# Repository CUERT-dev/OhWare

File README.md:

View this project on [CADLAB.io](https://cadlab.io/project/29674). 

# ObcSimplex

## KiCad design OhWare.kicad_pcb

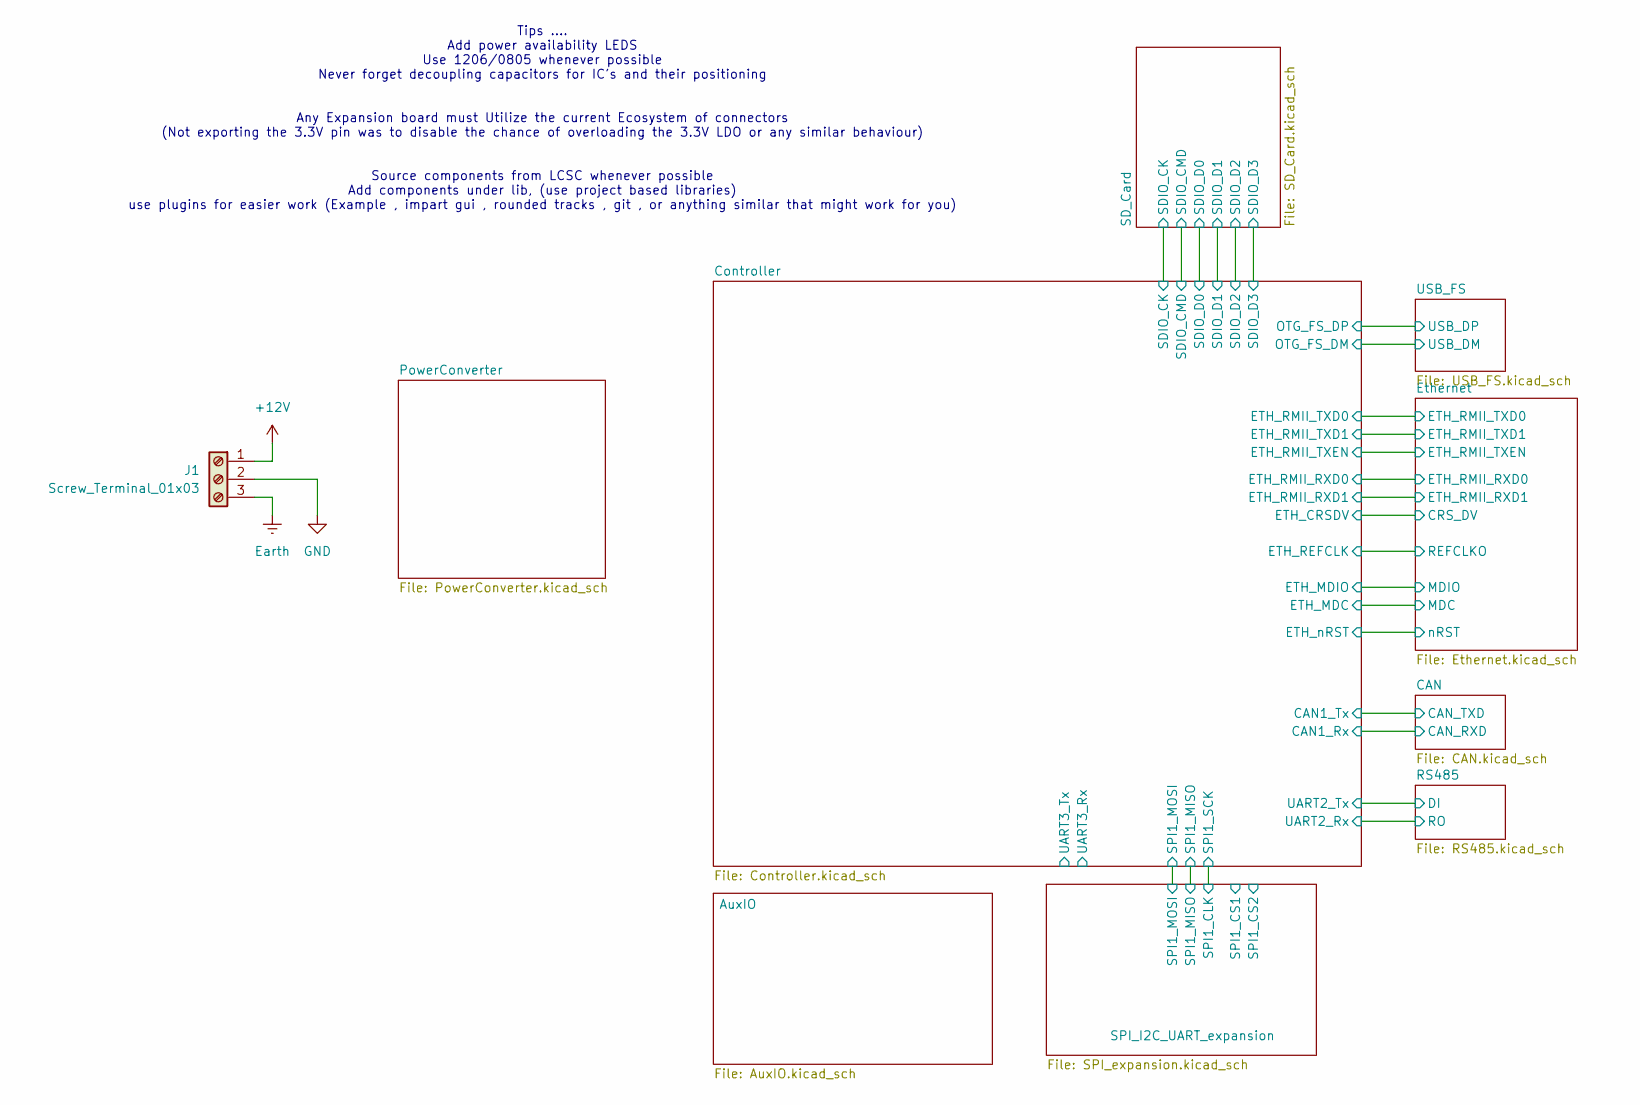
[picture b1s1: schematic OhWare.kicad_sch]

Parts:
J1: Screw_Terminal_01x03

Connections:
+12V: J1.1; also elsewhere on the board

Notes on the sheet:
Tips .... Add power availability LEDS Use 1206/0805 whenever possible Never forget decoupling capacitors for IC's and their positioning Any Expansion board must Utilize the current Ecosystem of connectors (Not exporting the 3.3V pin was to disable the chance of overloading the 3.3V LDO or any simil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

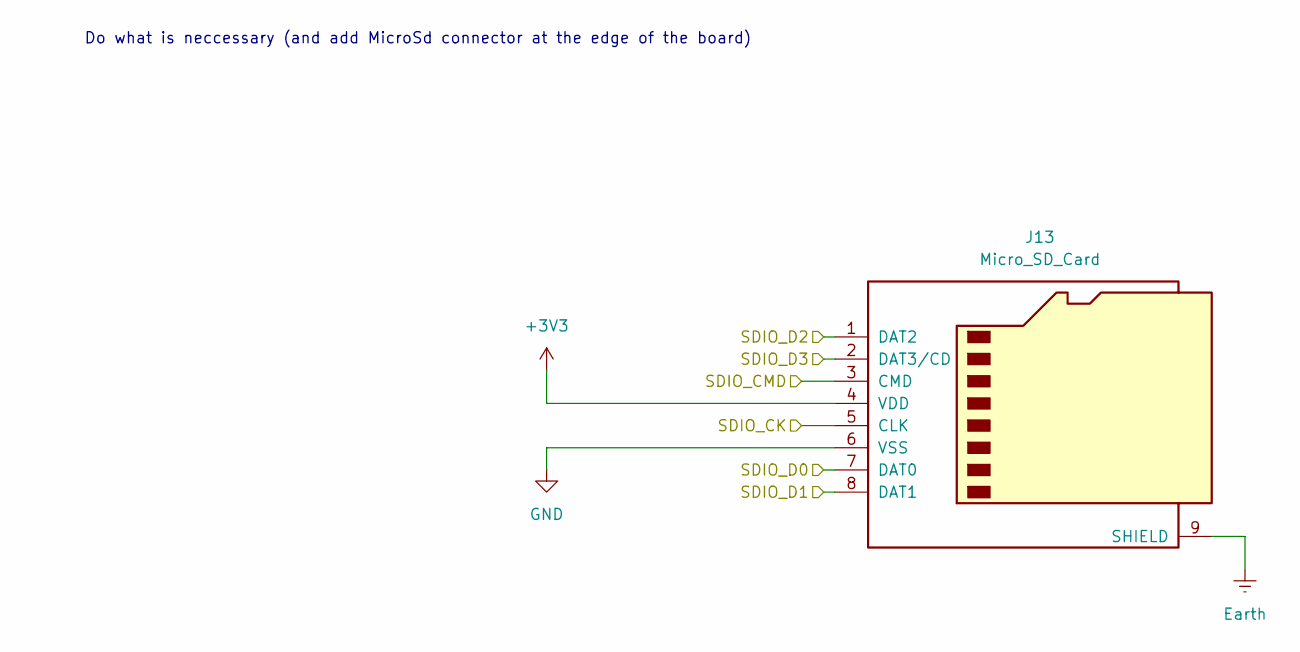
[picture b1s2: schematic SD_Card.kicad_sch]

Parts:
J13: Micro_SD_Card; microSD_HC_Molex_47219-2001

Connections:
+3V3: J13.4 (VDD); also elsewhere on the board
/Controller/SDIO_CK: J13.5 (CLK); also elsewhere on the board
/Controller/SDIO_CMD: J13.3 (CMD); also elsewhere on the board
/Controller/SDIO_D0: J13.7 (DAT0); also elsewhere on the board
/Controller/SDIO_D1: J13.8 (DAT1); also elsewhere on the board
/Controller/SDIO_D2: J13.1 (DAT2); also elsewhere on the board
/Controller/SDIO_D3: J13.2 (DAT3/CD); also elsewhere on the board

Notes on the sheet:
Do what is neccessary (and add MicroSd connector at the edge of the board)

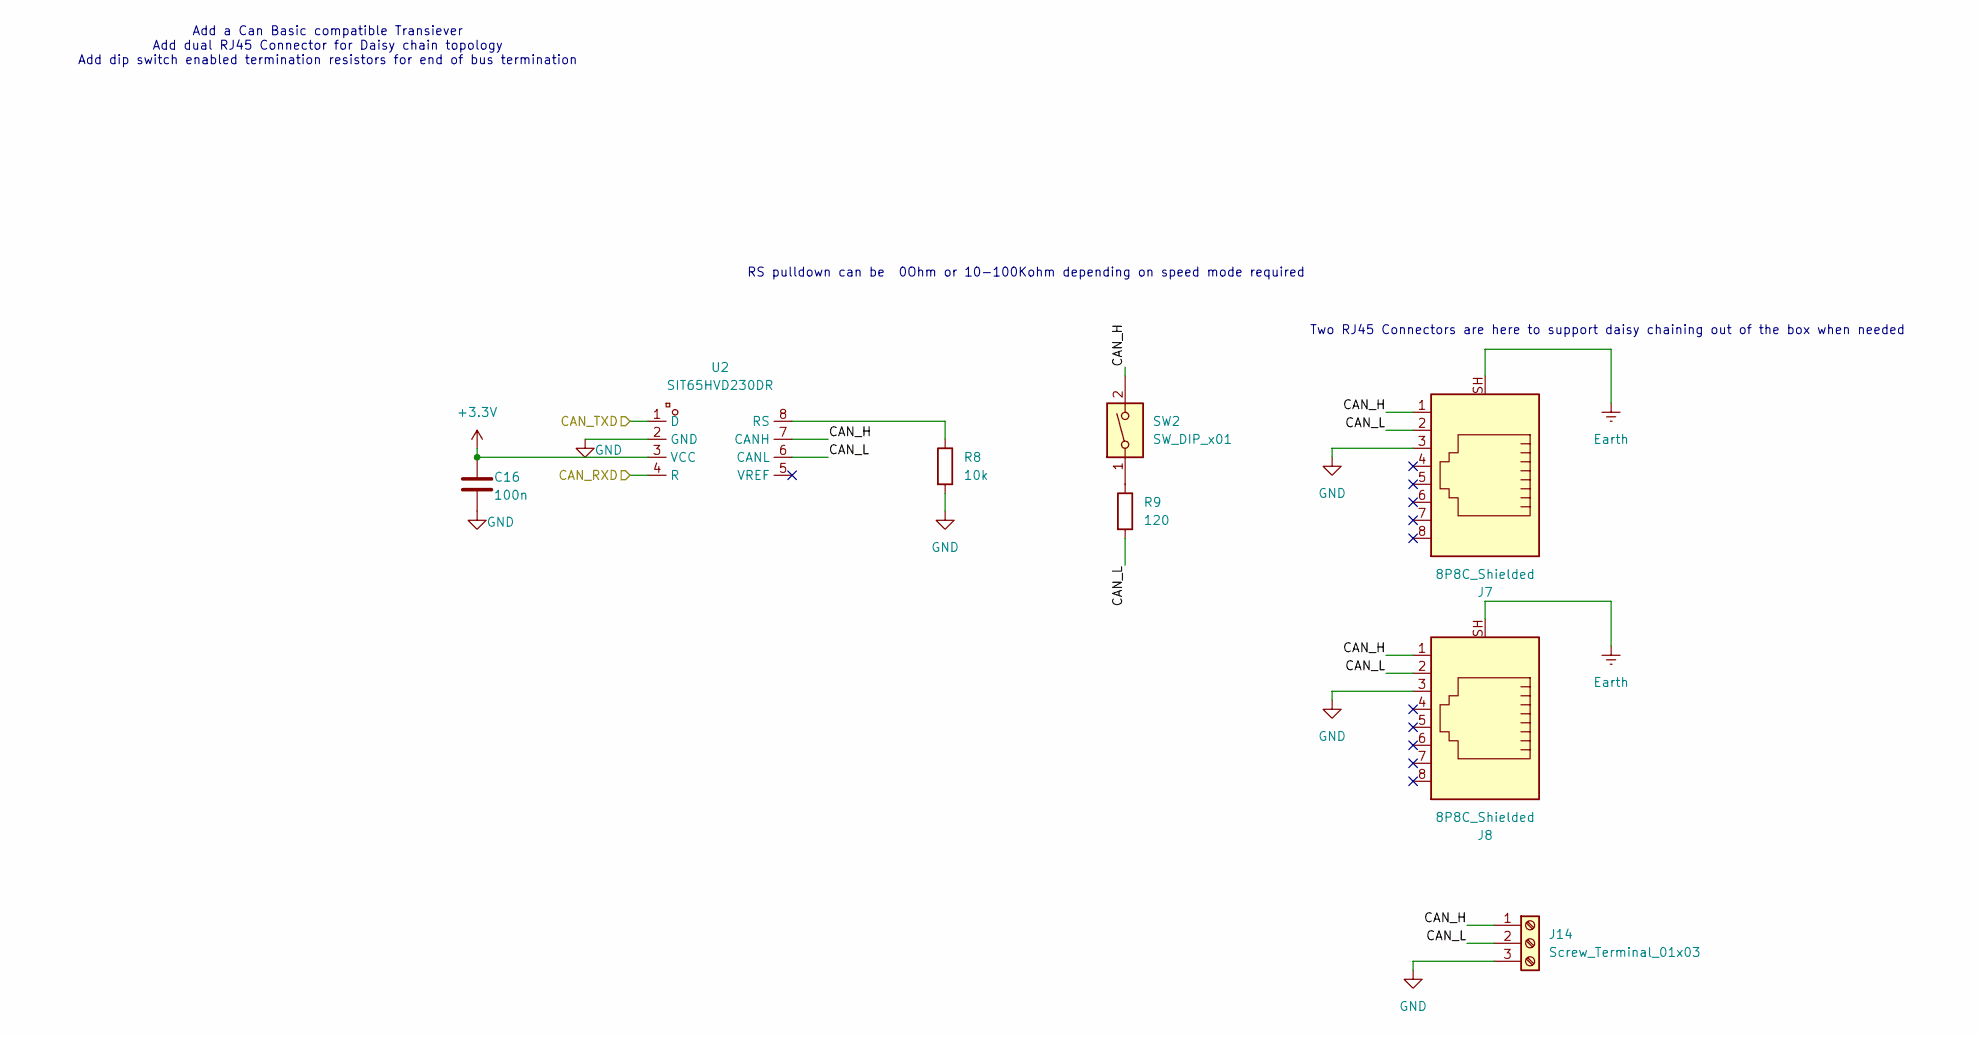
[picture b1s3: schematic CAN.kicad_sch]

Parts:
C16: 100n; C_0805_2012Metric
J7, J8: 8P8C_Shielded; RJ45_Ninigi_GE
J14: Screw_Terminal_01x03; TerminalBlock_Phoenix_PT-1,5-3-3.5-H_1x03_P3.50mm_Horizontal
R8: 10k; R_0805_2012Metric
R9: 120; R_0805_2012Metric
SW2: SW_DIP_x01; SW_DIP_SPSTx01_Slide_6.7x4.1mm_W7.62mm_P2.54mm_LowProfile
U2: SIT65HVD230DR; SOP-8_L4.9-W3.9-P1.27-LS6.0-BL; LCSC Part C496619

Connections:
+3.3V: C16.1, U2.3 (VCC); also elsewhere on the board
/CAN/CAN_L: J7.2, J8.2, J14.2, R9.2, U2.6 (CANL)
/CAN/CAN_RXD: U2.4 (R); also elsewhere on the board
/CAN/CAN_TXD: U2.1 (D); also elsewhere on the board
unnamed: R8.1, U2.8 (RS)

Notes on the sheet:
Add a Can Basic compatible Transiever Add dual RJ45 Connector for Daisy chain topology Add dip switch enabled termination resistors for end of bus termination
RS pulldown can be 0Ohm or 10-100Kohm depending on speed mode required
Two RJ45 Connectors are here to support daisy chaining out of the box when needed

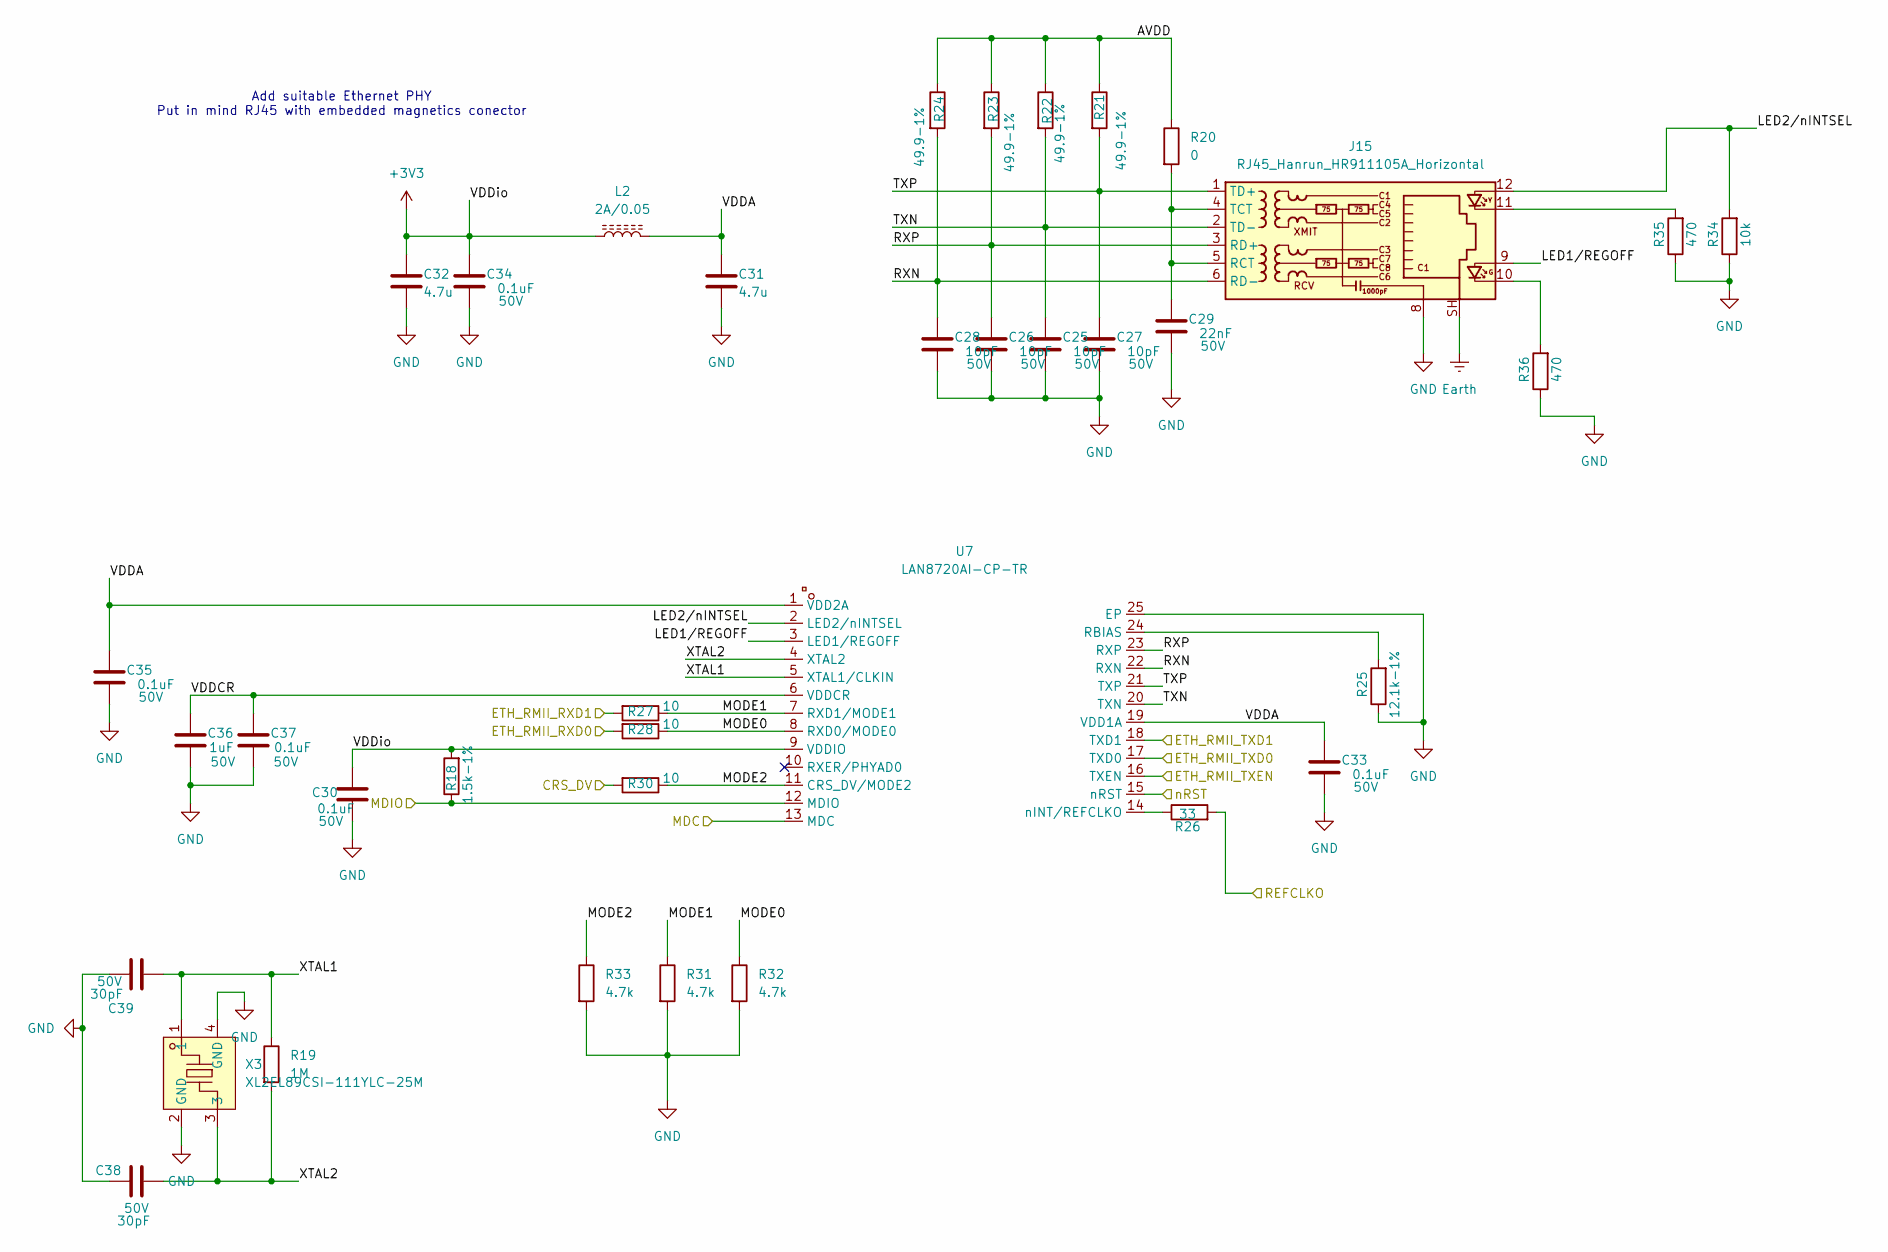
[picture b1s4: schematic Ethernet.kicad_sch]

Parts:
C25, C26, C27, C28: 10pF; C_0805_2012Metric; Voltage Rating 50V
C29: 22nF; C_0805_2012Metric; Voltage Rating 50V
C30, C33, C34, C35, C37: 0.1uF; C_0805_2012Metric; Voltage Rating 50V
C31, C32: 4.7u; C_0805_2012Metric
C36: 1uF; C_0805_2012Metric; Voltage Rating 50V
C38, C39: 30pF; C_0805_2012Metric; Voltage Rating 50V
J15: RJ45_Hanrun_HR911105A_Horizontal
L2: 2A/0.05; L_1206_3216Metric
R18: 1.5k-1%; R_0805_2012Metric
R19: 1M; R_0805_2012Metric
R20: 0; R_0805_2012Metric
R21, R22, R23, R24: 49.9-1%; R_0805_2012Metric
R25: 12.1k-1%; R_0805_2012Metric
R26: 33; R_0805_2012Metric
R27, R28, R30: 10; R_0805_2012Metric
R31, R32, R33: 4.7k; R_0805_2012Metric
R34: 10k; R_0805_2012Metric
R35, R36: 470; R_0805_2012Metric
U7: LAN8720AI-CP-TR; QFN-24_L4.0-W4.0-P0.50-BL-EP2.6; LCSC Part C17146
X3: XL2EL89CSI-111YLC-25M; CRYSTAL-SMD_4P-L3.2-W2.5-BL; LCSC Part C5280577

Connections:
+3V3: C30.1, C32.1, C34.1, L2.1, R18.2, U7.9 (VDDIO); also elsewhere on the board
/Controller/ETH_CRSDV: R30.2; also elsewhere on the board
/Controller/ETH_MDC: U7.13 (MDC); also elsewhere on the board
/Controller/ETH_MDIO: R18.1, U7.12 (MDIO); also elsewhere on the board
/Controller/ETH_REFCLK: R26.2; also elsewhere on the board
/Controller/ETH_RMII_RXD0: R28.2; also elsewhere on the board
/Controller/ETH_RMII_RXD1: R27.2; also elsewhere on the board
/Controller/ETH_RMII_TXD0: U7.17 (TXD0); also elsewhere on the board
/Controller/ETH_RMII_TXD1: U7.18 (TXD1); also elsewhere on the board
/Controller/ETH_RMII_TXEN: U7.16 (TXEN); also elsewhere on the board
/Controller/ETH_nRST: U7.15 (nRST); also elsewhere on the board
/Ethernet/AVDD: R20.1, R21.1, R22.1, R23.1, R24.1
/Ethernet/LED1/REGOFF: J15.9, U7.3 (LED1/REGOFF)
/Ethernet/LED2/nINTSEL: J15.12, R34.2, U7.2 (LED2/nINTSEL)
/Ethernet/MODE0: R28.1, R32.1, U7.8 (RXD0/MODE0)
/Ethernet/MODE1: R27.1, R31.1, U7.7 (RXD1/MODE1)
/Ethernet/MODE2: R30.1, R33.1, U7.11 (CRS_DV/MODE2)
/Ethernet/RXN: C28.1, J15.6 (RD-), R24.2, U7.22 (RXN)
/Ethernet/RXP: C26.1, J15.3 (RD+), R23.2, U7.23 (RXP)
/Ethernet/TXN: C25.1, J15.2 (TD-), R22.2, U7.20 (TXN)
/Ethernet/TXP: C27.1, J15.1 (TD+), R21.2, U7.21 (TXP)
/Ethernet/VDDA: C31.1, C33.1, C35.1, L2.2, U7.1 (VDD2A), U7.19 (VDD1A)
/Ethernet/VDDCR: C36.1, C37.1, U7.6 (VDDCR)
/Ethernet/XTAL1: C39.2, R19.1, U7.5 (XTAL1/CLKIN), X3.1
/Ethernet/XTAL2: C38.2, R19.2, U7.4 (XTAL2), X3.3
unnamed: J15.10, R36.2
unnamed: J15.11, R35.2
unnamed: C29.1, J15.4 (TCT), J15.5 (RCT), R20.2
unnamed: R25.2, U7.24 (RBIAS)
unnamed: R26.1, U7.14 (nINT/REFCLKO)

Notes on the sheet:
Add suitable Ethernet PHY Put in mind RJ45 with embedded magnetics conector

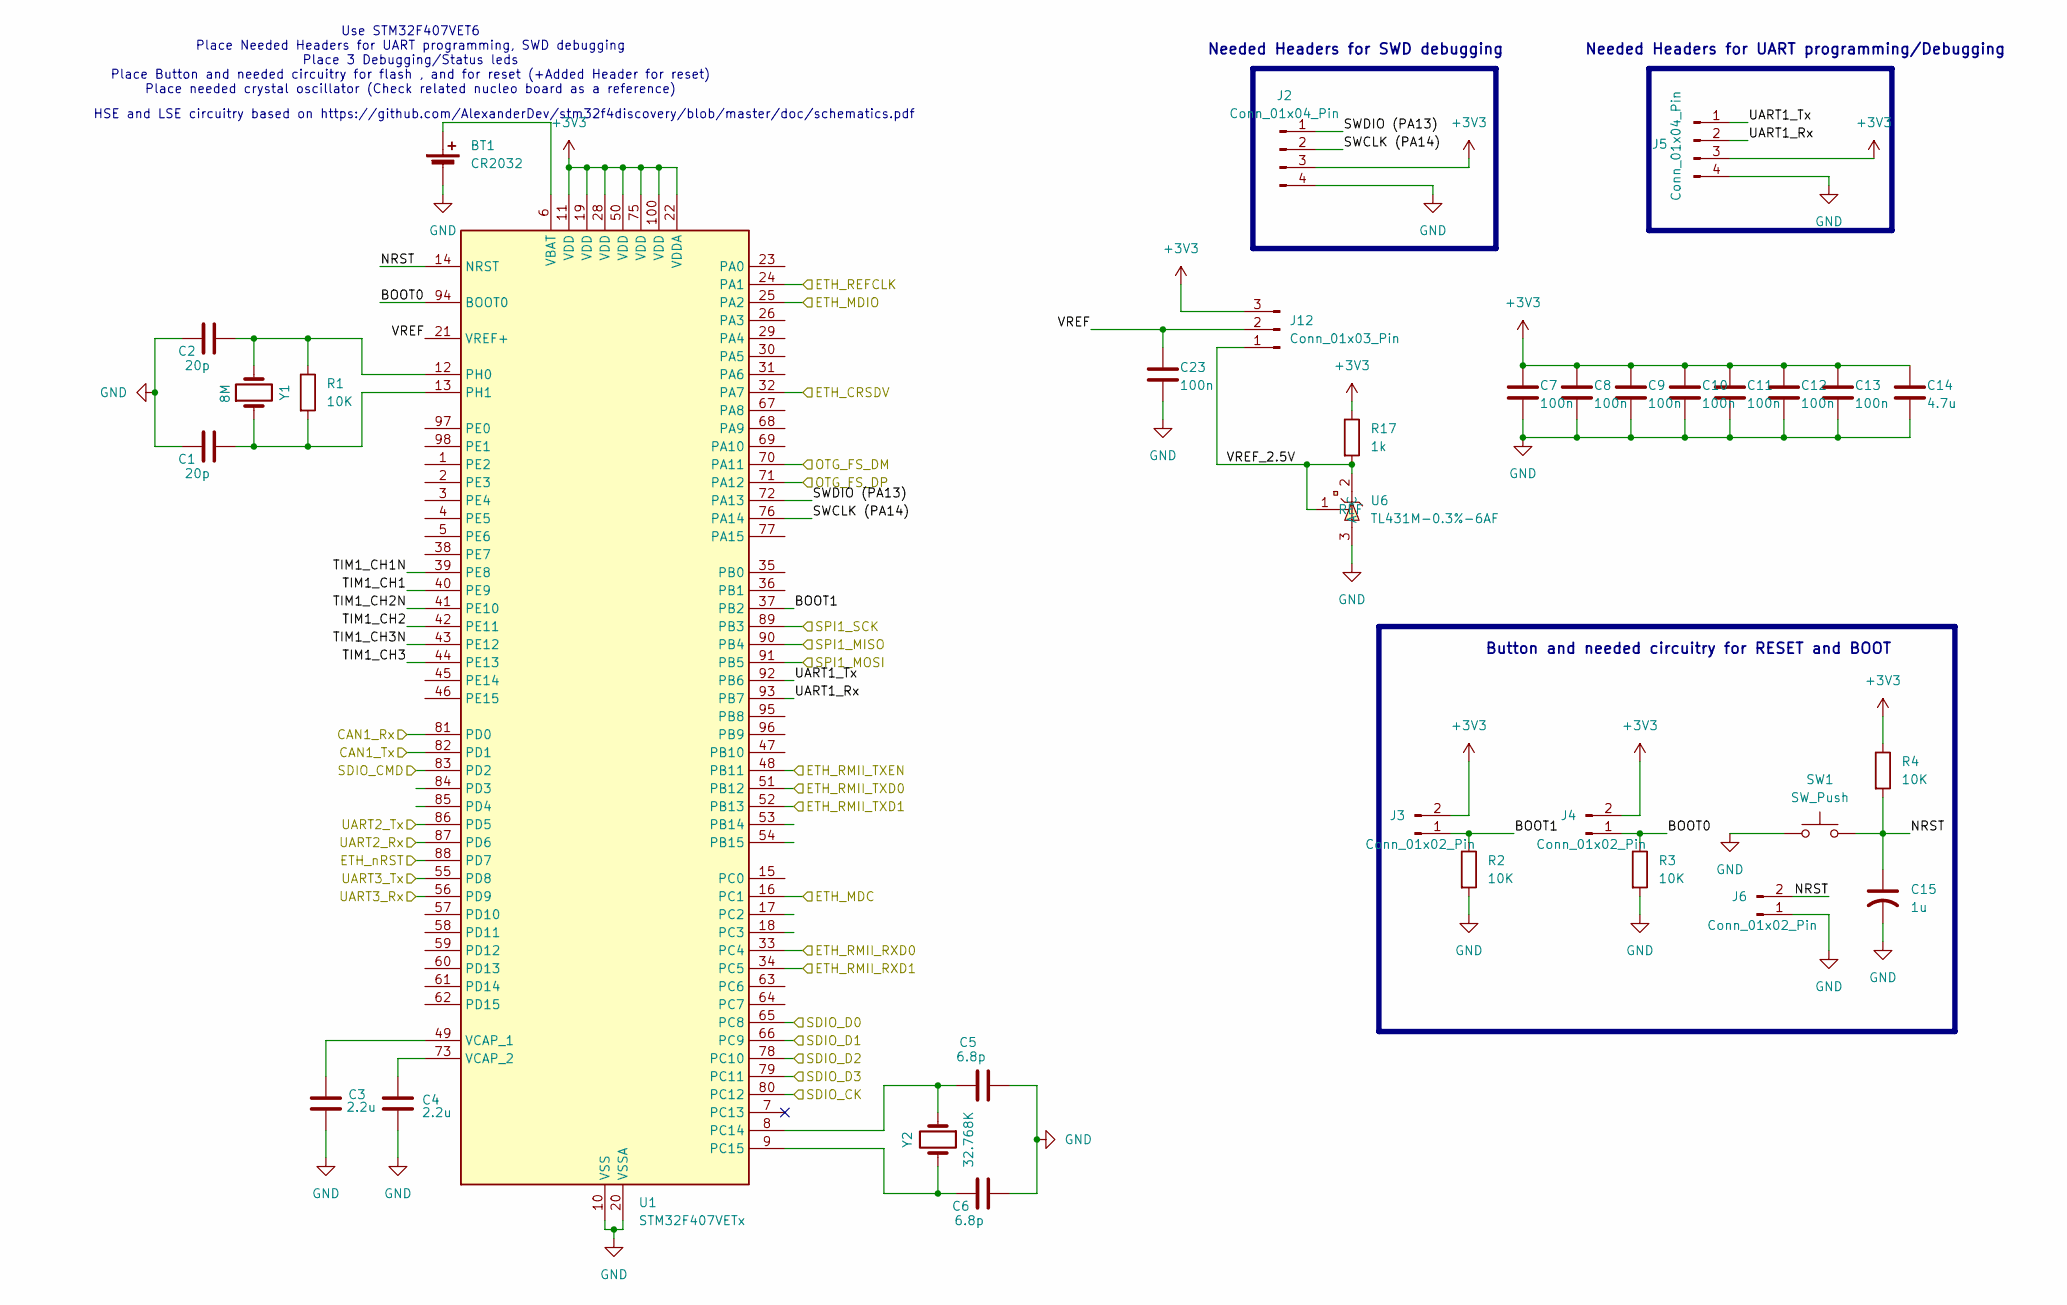
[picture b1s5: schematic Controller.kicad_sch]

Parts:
BT1: CR2032; BAT_1074
C1, C2: 20p
C3, C4: 2.2u
C5, C6: 6.8p
C7, C8, C9, C10, C11, C12, C13, C23: 100n
C14: 4.7u
C15: 1u
J2, J5: Conn_01x04_Pin
J3, J4, J6: Conn_01x02_Pin
J12: Conn_01x03_Pin
R1, R2, R3, R4: 10K
R17: 1k
SW1: SW_Push
U1: STM32F407VETx; LQFP-100_14x14mm_P0.5mm
U6: TL431M-0.3%-6AF; SOT-23-3_L2.9-W1.6-P1.90-LS2.8-BR; LCSC Part C48947167
Y1: 8M
Y2: 32.768K

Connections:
+3V3: C7.1, C8.1, C9.1, C10.1, C11.1, C12.1, C13.1, C14.1, J2.3, J3.2, J4.2, J5.3, J12.3, R4.1, R17.1, U1.11 (VDD), U1.19 (VDD), U1.22 (VDDA), U1.28 (VDD), U1.50 (VDD), U1.75 (VDD), U1.100 (VDD); also elsewhere on the board
/CAN/CAN_RXD: U1.81 (PD0); also elsewhere on the board
/CAN/CAN_TXD: U1.82 (PD1); also elsewhere on the board
/Controller/BOOT0: J4.1, R3.1, U1.94 (BOOT0)
/Controller/BOOT1: J3.1, R2.1, U1.37 (PB2)
/Controller/ETH_CRSDV: U1.32 (PA7); also elsewhere on the board
/Controller/ETH_MDC: U1.16 (PC1); also elsewhere on the board
/Controller/ETH_MDIO: U1.25 (PA2); also elsewhere on the board
/Controller/ETH_REFCLK: U1.24 (PA1); also elsewhere on the board
/Controller/ETH_RMII_RXD0: U1.33 (PC4); also elsewhere on the board
/Controller/ETH_RMII_RXD1: U1.34 (PC5); also elsewhere on the board
/Controller/ETH_RMII_TXD0: U1.51 (PB12); also elsewhere on the board
/Controller/ETH_RMII_TXD1: U1.52 (PB13); also elsewhere on the board
/Controller/ETH_RMII_TXEN: U1.48 (PB11); also elsewhere on the board
/Controller/ETH_nRST: U1.88 (PD7); also elsewhere on the board
/Controller/I2C1_SCL: U1.95 (PB8); also elsewhere on the board
/Controller/I2C1_SDA: U1.96 (PB9); also elsewhere on the board
/Controller/OTG_FS_DM: U1.70 (PA11); also elsewhere on the board
/Controller/OTG_FS_DP: U1.71 (PA12); also elsewhere on the board
/Controller/SDIO_CK: U1.80 (PC12); also elsewhere on the board
/Controller/SDIO_CMD: U1.83 (PD2); also elsewhere on the board
/Controller/SDIO_D0: U1.65 (PC8); also elsewhere on the board
/Controller/SDIO_D1: U1.66 (PC9); also elsewhere on the board
/Controller/SDIO_D2: U1.78 (PC10); also elsewhere on the board
/Controller/SDIO_D3: U1.79 (PC11); also elsewhere on the board
/Controller/SPI1_CS1: U1.45 (PE14); also elsewhere on the board
/Controller/SPI1_CS2: U1.46 (PE15); also elsewhere on the board
/Controller/SPI1_MISO: U1.90 (PB4); also elsewhere on the board
/Controller/SPI1_MOSI: U1.91 (PB5); also elsewhere on the board
/Controller/SPI1_SCK: U1.89 (PB3); also elsewhere on the board
/Controller/SWCLK (PA14): J2.2, U1.76 (PA14)
/Controller/SWDIO (PA13): J2.1, U1.72 (PA13)
/Controller/TIM1_CH1: U1.40 (PE9)
/Controller/TIM1_CH1N: U1.39 (PE8)
/Controller/TIM1_CH2: U1.42 (PE11)
/Controller/TIM1_CH2N: U1.41 (PE10)
/Controller/TIM1_CH3: U1.44 (PE13)
/Controller/TIM1_CH3N: U1.43 (PE12)
/Controller/UART1_Rx: J5.2, U1.93 (PB7)
/Controller/UART1_Tx: J5.1, U1.92 (PB6)
/Controller/UART2_Rx: U1.87 (PD6); also elsewhere on the board
/Controller/UART2_Tx: U1.86 (PD5); also elsewhere on the board
/Controller/UART3_Rx: U1.56 (PD9); also elsewhere on the board
/Controller/UART3_Tx: U1.55 (PD8); also elsewhere on the board
/Controller/UART6_Rx: U1.64 (PC7); also elsewhere on the board
/Controller/UART6_Tx: U1.63 (PC6); also elsewhere on the board
/Controller/VREF: C23.1, J12.2, U1.21 (VREF+)
/Controller/VREF_2.5V: J12.1, R17.2, U6.1 (REF), U6.2 (C)
unnamed: BT1.1 (+), U1.6 (VBAT)
unnamed 89: C5.1, U1.8 (PC14), Y2.1; also elsewhere on the board
unnamed 90: C6.1, U1.9 (PC15), Y2.2; also elsewhere on the board
unnamed 91: C1.2, R1.2, U1.13 (PH1); also elsewhere on the board
unnamed: C3.1, U1.49 (VCAP_1)
unnamed: C4.1, U1.73 (VCAP_2)

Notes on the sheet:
HSE and LSE circuitry based on https://github.com/AlexanderDev/stm32f4discovery/blob/master/doc/schematics.pdf
Needed Headers for UART programming/Debugging
Needed Headers for SWD debugging
Button and needed circuitry for RESET and BOOT
Use STM32F407VET6 Place Needed Headers for UART programming, SWD debugging Place 3 Debugging/Status leds Place Button and needed circuitry for flash , and for reset (+Added Header for reset) Place needed crystal oscillator (Check related nucleo board as a reference)

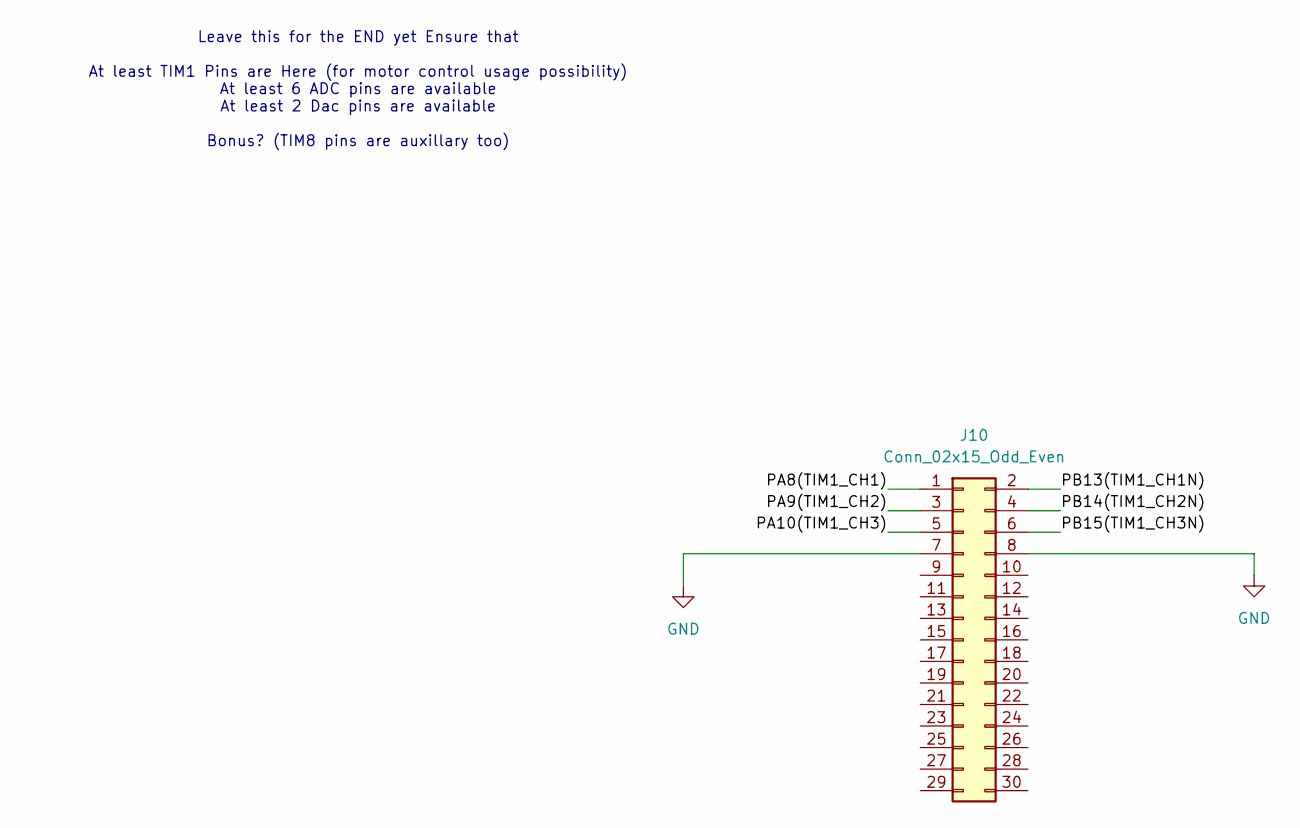
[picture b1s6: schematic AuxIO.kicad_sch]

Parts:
J10: Conn_02x15_Odd_Even

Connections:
unnamed: J10.7, J10.8

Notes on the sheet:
Leave this for the END yet Ensure that At least TIM1 Pins are Here (for motor control usage possibility) At least 6 ADC pins are available At least 2 Dac pins are available Bonus? (TIM8 pins are auxillary too)

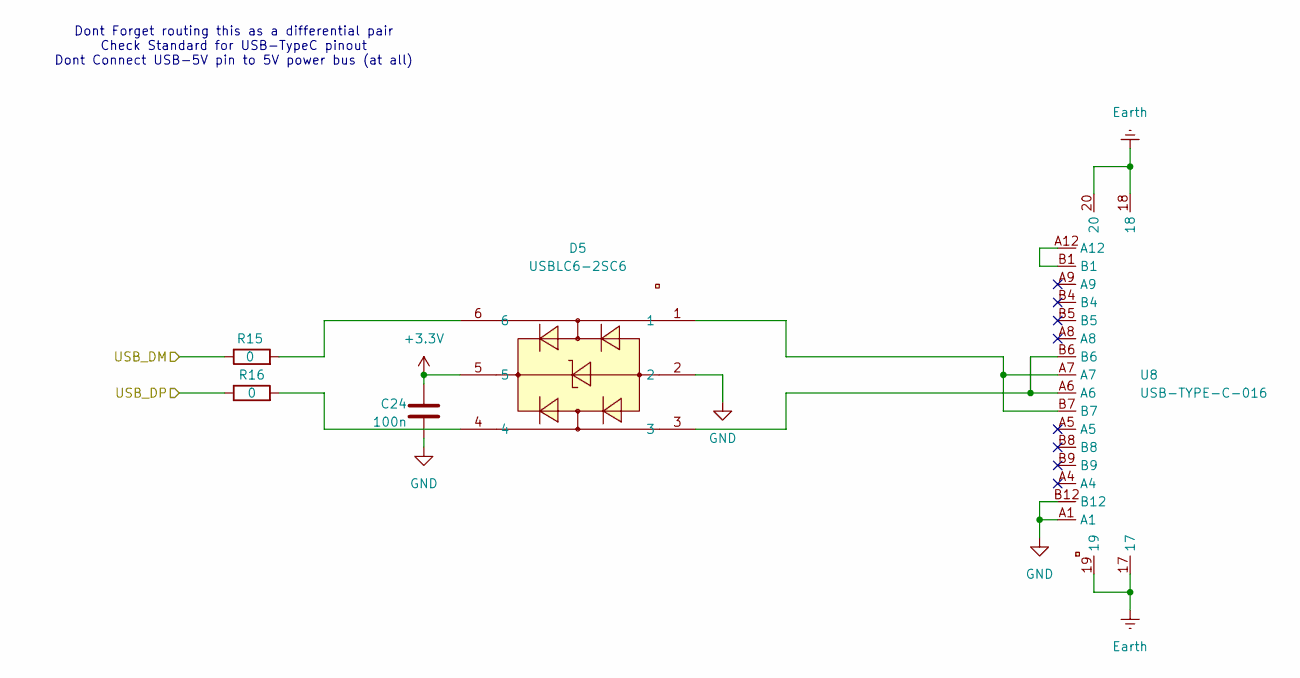
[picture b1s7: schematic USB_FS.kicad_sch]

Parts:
C24: 100n; C_0805_2012Metric
D5: USBLC6-2SC6; SOT-23-6_L2.9-W1.6-P0.95-LS2.8-BL; LCSC Part C7519
R15, R16: 0; R_0805_2012Metric
U8: USB-TYPE-C-016; USB-SMD_TYPE-C16PCB1.6073; LCSC Part C2927036

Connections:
+3.3V: C24.1, D5.5; also elsewhere on the board
/Controller/OTG_FS_DM: R15.1; also elsewhere on the board
/Controller/OTG_FS_DP: R16.1; also elsewhere on the board
unnamed: D5.1, U8.A7, U8.B7
unnamed: D5.3, U8.A6, U8.B6
unnamed: D5.4, R16.2
unnamed: D5.6, R15.2

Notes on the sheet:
Dont Forget routing this as a differential pair Check Standard for USB-TypeC pinout Dont Connect USB-5V pin to 5V power bus (at all)

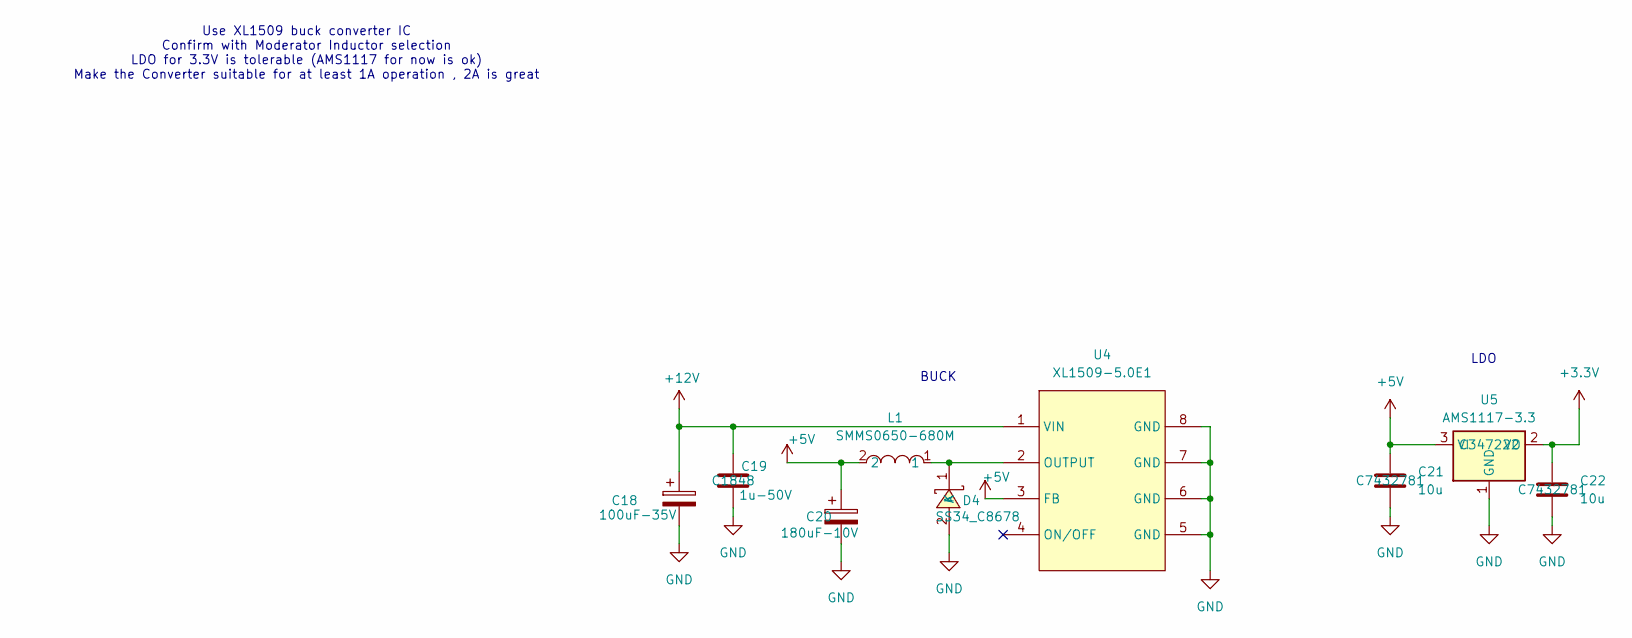
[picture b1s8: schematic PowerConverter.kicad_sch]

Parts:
C18: 100uF-35V; CP_Radial_D6.3mm_P2.50mm
C19: 1u-50V; C_1206_3216Metric_Pad1.33x1.80mm_HandSolder; LCSC Part C1848
C20: 180uF-10V; CP_Radial_D6.3mm_P2.50mm
C21, C22: 10u; C_1206_3216Metric_Pad1.33x1.80mm_HandSolder; LCSC Part C7432781
D4: SS34_C8678; SMA_L4.3-W2.6-LS5.2-RD; LCSC Part C8678
L1: SMMS0650-680M; IND-SMD_L7.1-W6.6_H5.0; LCSC Part C2894721
U4: XL1509-5.0E1; SOIC-8_L5.0-W4.0-P1.27-LS6.0-BL; LCSC Part C61063
U5: AMS1117-3.3; SOT-223-3_TabPin2_NOSILKSCREEN; LCSC Part C347222

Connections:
+3.3V: C22.1, U5.2 (VO); also elsewhere on the board
+5V: C20.1, C21.1, L1.2, U4.3 (FB), U5.3 (VI); also elsewhere on the board
+12V: C18.1, C19.1, U4.1 (VIN); also elsewhere on the board
unnamed: D4.1 (K), L1.1, U4.2 (OUTPUT)

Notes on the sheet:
LDO
BUCK
Use XL1509 buck converter IC Confirm with Moderator Inductor selection LDO for 3.3V is tolerable (AMS1117 for now is ok) Make the Converter suitable for at least 1A operation , 2A is great

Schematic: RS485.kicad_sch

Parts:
C17: 0.1u; C_0805_2012Metric
J11: Screw_Terminal_01x05; TerminalBlock_Phoenix_PT-1,5-5-3.5-H_1x05_P3.50mm_Horizontal
R14: 120; R_0805_2012Metric
SW3: SW_DIP_x03; SW_DIP_SPSTx03_Slide_6.7x9.18mm_W7.62mm_P2.54mm_LowProfile
U3: SIT3490EESA; SOP-8_L4.9-W3.9-P1.27-LS6.0-BL; LCSC Part C496618

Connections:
+3.3V: C17.1, U3.1 (VCC); also elsewhere on the board
/Controller/UART2_Rx: U3.2 (RO); also elsewhere on the board
/Controller/UART2_Tx: U3.3 (DI); also elsewhere on the board
/RS485/A: J11.3, SW3.1, SW3.2, U3.8 (A)
/RS485/B: J11.4, R14.2, SW3.3, U3.7 (B)
/RS485/Y: J11.1, SW3.4, U3.5 (Y)
/RS485/Z: J11.2, SW3.5, U3.6 (Z)
unnamed: R14.1, SW3.6

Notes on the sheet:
Use DB9 connector Use Suitable Rs485 transiever
RS485 Full-Duplex Tranciver
The dip switch array adds optional Termination and Half-Duplex mode 1-6 closed (Termination enabled between A-B) 2-5 closed and 3-4 closed (A-Z and B-Y shorted) for half duplex mode (Software realization should be added for self talk ignorance)

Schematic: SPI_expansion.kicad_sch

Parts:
J9, J16: Conn_02x05_Odd_Even; IDC-Header_2x05_P2.54mm_Vertical
J17, J18, J19: Conn_02x03_Odd_Even; IDC-Header_2x03_P2.54mm_Vertical
R5, R6, R7, R10, R11, R12, R13, R29: 0; R_0805_2012Metric

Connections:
+5V: J9.1, J16.1; also elsewhere on the board
/Controller/I2C1_SCL: J19.3; also elsewhere on the board
/Controller/I2C1_SDA: J19.1; also elsewhere on the board
/Controller/SPI1_CS1: R7.1; also elsewhere on the board
/Controller/SPI1_CS2: R29.1; also elsewhere on the board
/Controller/SPI1_MISO: R5.1, R12.1; also elsewhere on the board
/Controller/SPI1_MOSI: R10.1, R11.1; also elsewhere on the board
/Controller/SPI1_SCK: R6.1, R13.1; also elsewhere on the board
/Controller/UART3_Rx: J17.3; also elsewhere on the board
/Controller/UART3_Tx: J17.1; also elsewhere on the board
/Controller/UART6_Rx: J18.3; also elsewhere on the board
/Controller/UART6_Tx: J18.1; also elsewhere on the board
unnamed: J9.3, R10.2
unnamed: J9.5, R5.2
unnamed: J9.7, R6.2
unnamed: J9.9, R7.2
unnamed: J16.3, R11.2
unnamed: J16.5, R12.2
unnamed: J16.7, R13.2
unnamed: J16.9, R29.2

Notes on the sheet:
Add 1-2x I2C with suitable pullup resistor placeholders
Add 1-2x UARTs (no strict Requirements)
This module is always an SPI master and is always connected to Slaves Place 0Ohm resistor placeholders for SPI master termination (enhances signal integrity for high speed spi) S-G-S-G is also employed for high speed SPI signal integrity Export Only One SPI with 3 CS PINS (a CS for each connector/p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

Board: 2 copper layers, 110 parts (0 on the bottom side), 96 nets, no tracks yet.

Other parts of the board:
X1: X32258MOB4SI; CRYSTAL-SMD_4P-L3.2-W2.5-BL
X2: ABS07-32.768KHZ-T; OSC-SMD_2P-L3.2-W1.5

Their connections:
unnamed 89: X2.2 (OSC2); also elsewhere on the board
unnamed 90: X2.1 (OSC1); also elsewhere on the board
unnamed 91: X1.1; also elsewhere on the board

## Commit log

2025-10-10 Backlink to CADLAB.io has been added.
2025-10-16 Your commit message here
2025-10-31 Latest updates
2025-11-01 Latest changes (added SD , USB , CAN , RS485)
2025-11-01 added Ethernet and SPI interface
2025-11-01 Schematic--Footprint link
